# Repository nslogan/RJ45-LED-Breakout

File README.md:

# RJ45-LED-Breakout

## Description

Simple breakout board for an RJ45 with LEDs. Has two 0805 resistor pads tied to Vin with pins for LED1/2-. Has solder pads for both shield legs to optionally tie to ground. Intended for use with Amphenol RJHSE-548x series. You can find [this project on GitHub](https://github.com/nslogan/RJ45-LED-Breakout). Fits breadboard well with headers 0.9" apart.

## Production

The board measured 0.65x1.20in (17x30mm) and was designed for production at [OSH Park](https://www.oshpark.com/). The OSHPark DRU is located in the `res/` folder.

The boards can be purchased [here](https://www.oshpark.com/shared_projects/6Iadx5r2) @ $3.90 for three.

## Parts

All parts on this board are from the [LoganSmith-Eagle-Library](https://github.com/nslogan/LoganSmith-Eagle-Library) available on GitHub (work in progress).

The BOM is located in the release folder, all parts are sourced from Digi-Key.

## Project Structure

This project adheres to this structure:

	[ProjectName]
		README.md
		[release]
			[Major.Minor]
				ProjectName_BOM_Major.Minor.xls or ProjectName_BOM_BOM_Major.Minor.csv
				ProjectName_schematic_Major.Minor.pdf
				ProjectName_board-<top/mid#/bottom>_Major.Minor.png
				ProjectName_Major.Minor.sch
				ProjectName_Major.Minor.brd
				[Gerbers]
					...
			...
		[src]
			[Major.0]
				BoardName.sch
				BoardName.brd
				BOM.xls or BOM.csv
			[Major+1.0]
				...
			...
		[lib]
			...
		[res]
			Manufacturer.dru
			Manufacturer.cam

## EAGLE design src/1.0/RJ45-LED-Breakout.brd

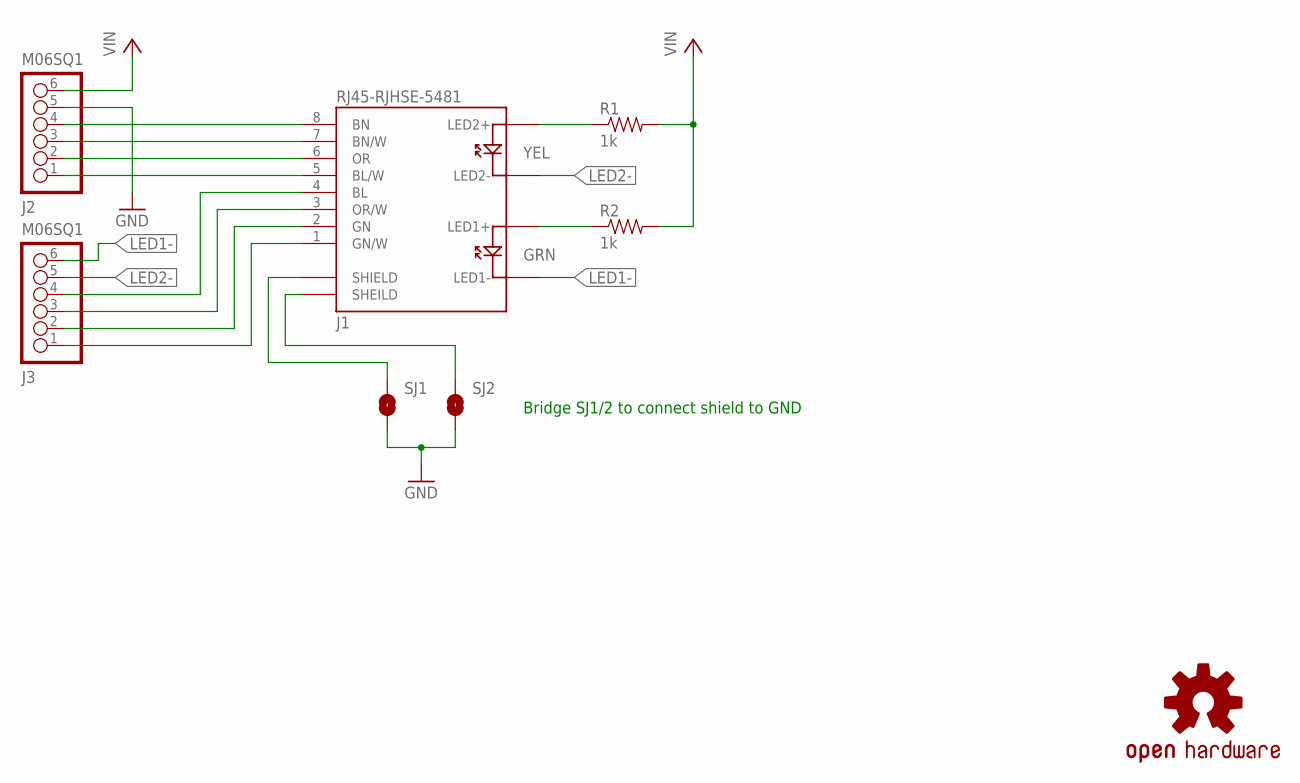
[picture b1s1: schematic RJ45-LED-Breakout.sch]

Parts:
J1: RJ45-RJHSE-5481; RJ45-RJHSE
J2, J3: M06SQ1; 1X06_SQ1
LOGO1: OSHW-LOGOM; OSHW-LOGO-M
R1, R2: 1k; 0805-RES
SJ1, SJ2: SJ_1WAY; SJ_2

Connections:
GND: J2.5, SJ1.2, SJ2.2
LED1+: J1.LED1+, R2.P$1 (1)
LED1-: J1.LE1D- (LED1-), J3.6
LED2+: J1.LED2+, R1.P$1 (1)
LED2-: J1.LED2-, J3.5
unnamed: J1.5 (BL/W), J2.1
unnamed: J1.6 (OR), J2.2
unnamed: J1.7 (BN/W), J2.3
unnamed: J1.8 (BN), J2.4
unnamed: J1.4 (BL), J3.4
unnamed: J1.3 (OR/W), J3.3
unnamed: J1.2 (GN), J3.2
unnamed: J1.1 (GN/W), J3.1
unnamed: J1.SHIELD@0 (SHIELD), SJ1.1
unnamed: J1.SHEILD@1 (SHEILD), SJ2.1
VIN: J2.6, R1.P$2 (2), R2.P$2 (2)

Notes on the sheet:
Bridge SJ1/2 to connect shield to GND

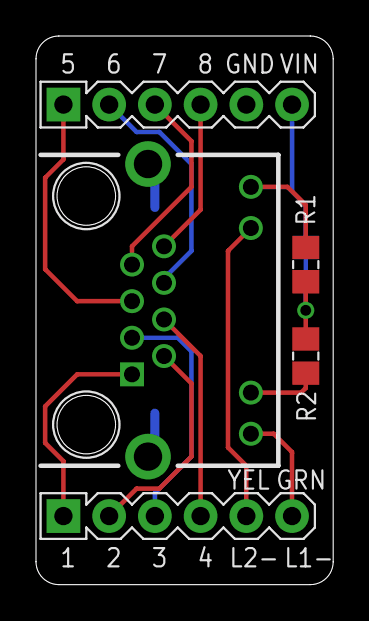
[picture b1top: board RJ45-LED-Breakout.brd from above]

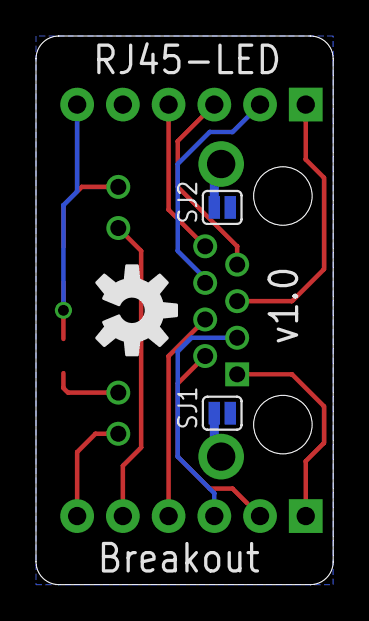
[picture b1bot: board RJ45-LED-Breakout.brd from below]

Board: 2 copper layers, 16.5 x 30.5 mm, 8 parts (3 on the bottom side), 16 nets.

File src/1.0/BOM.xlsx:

Part | QTY | Package | Description | DIGIKEY_OC | MFR | MPN | TEMP_RANGE | THICK | VALUE
J1 | 1 | RJ45-RJHSE | Shielded CAT5 RJ45 90 w/ LED and board lock | RJHSE-5481-ND | Amphenol Commercial Products | RJHSE-5481 | -55C to 85C | 0.530in | RJ45
J2,J3 | 2 | 1x6 | 1x8 Headers Gold 15uin | 609-3256-ND | FCI | 68000-206HLF |  | 0.230in | 1x6
R1,R2 | 2 | 0805 | 1k 5% 0805 RES 0.125W | P1.0KACT-ND | Panasonic Electronic Components | ERJ-6GEYJ102V |  | 0.70mm | 1k

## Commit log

2014-08-07 Initial commit. Need to add solder jumper to connect shield and ground (normally open) and lay out board. May move some of the pins around depending on how the layout goes.
2014-08-07 Created README.md
2014-08-07 Switching to develop branch.
2014-08-07 Board mostly laid out but pins 7/8 are switched. Fix that then reroute and it is basicaly done. Need to add some more info on silk.
2014-08-07 Almost ready for release. Need to create BOM and review all connections. Also look over schematic and possibly clean things up if necessary.
2014-08-08 Board has been ordered. Updated README, finalized board layout and silk. Need to create BOM and release 1.0.
2014-08-08 Release 1.0 ready to go, gonna double check a few things and merge to master.
2014-09-01 Added photos of the final product.
2014-09-01 I'm breaking my release pattern right now cause I'm still figuring out exactly how the release folder is structured (plus I didn't have these photos yet).

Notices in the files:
parts and their libraries:
SparkFun-Aesthetics: Licensing: Creative Commons ShareAlike 4.0 International - https://creativecommons.org/licenses/by-sa/4.0
